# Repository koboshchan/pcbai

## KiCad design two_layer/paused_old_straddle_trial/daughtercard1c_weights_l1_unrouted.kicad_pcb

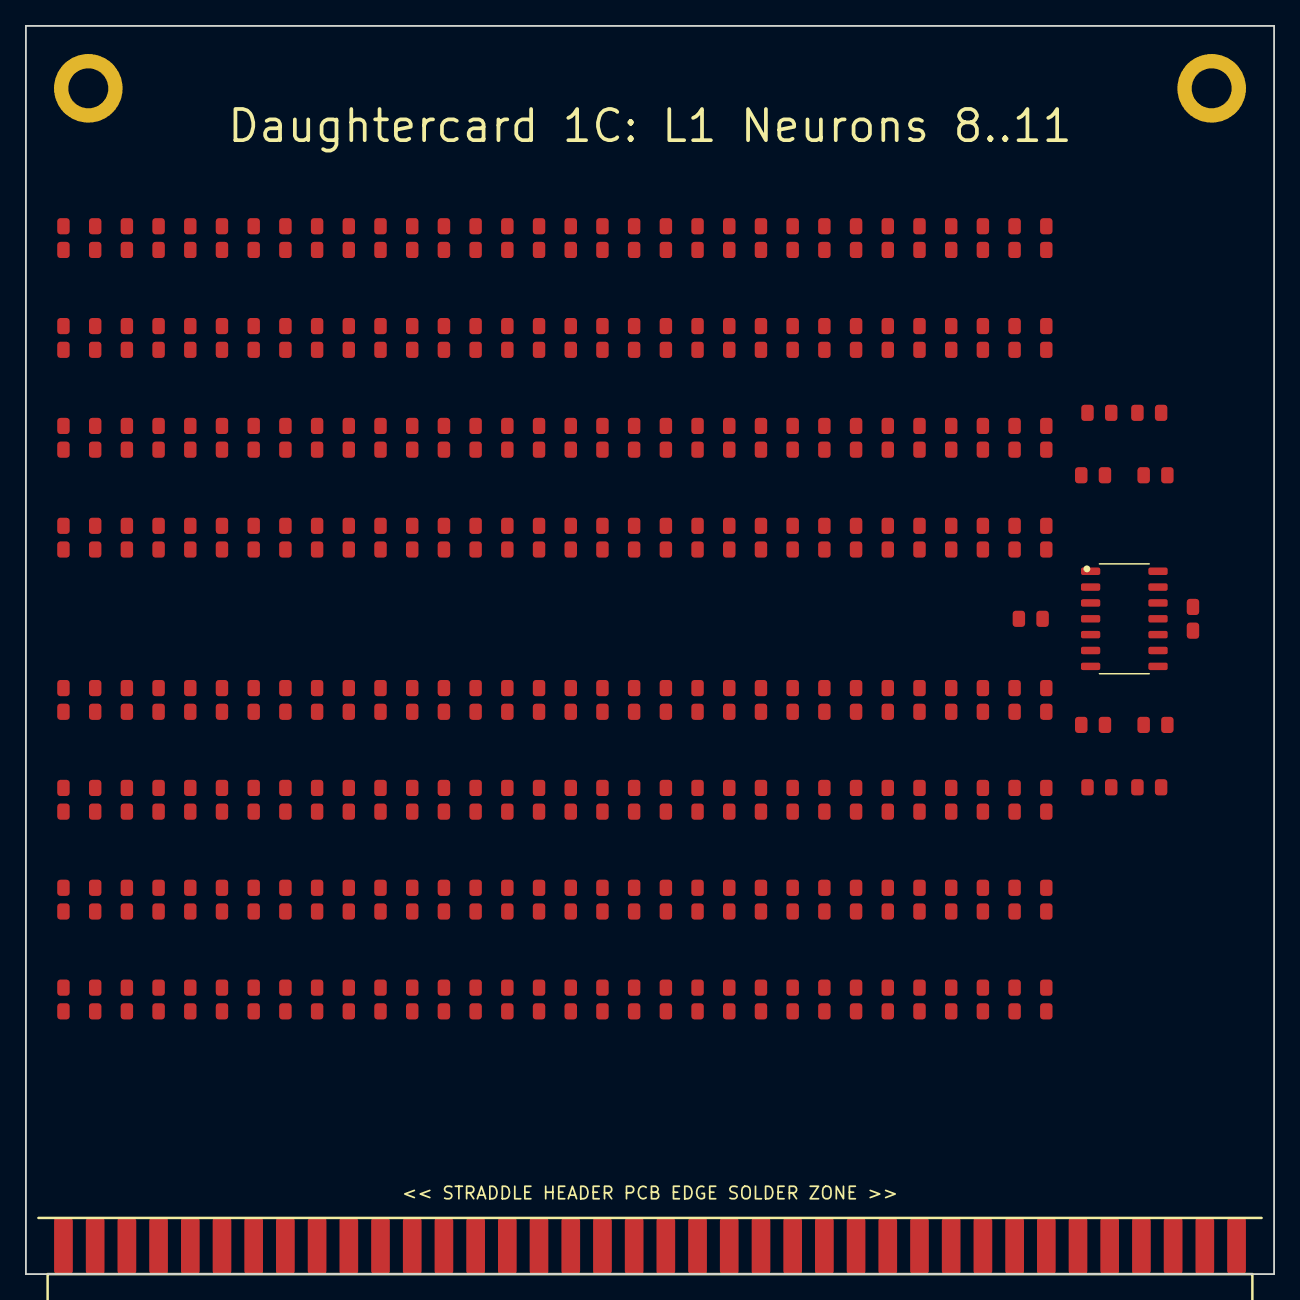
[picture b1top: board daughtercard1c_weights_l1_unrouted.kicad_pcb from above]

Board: 2 copper layers, 100.0 x 100.0 mm, 270 parts (0 on the bottom side), 77 nets, no tracks yet.

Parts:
C_U1N, C_U1P: 0.1uF; C_0805_2012Metric
H1, H2: MountingHole; MountingHole_3.2mm_M3_Pad
J_STRADDLE_EDGE: PinHeader_2x38_Straddle; PinHeader_2x38_Straddle_P2.54mm
R1_0_0, R1_1_0, R1_4_2, R1_5_2, R1_9_1, R1_10_1, R1_11_0, R1_12_0, R1_12_2, R1_16_0, R1_19_1, R1_20_1, R1_22_1, R1_23_2, R1_25_2, R1_28_2, R1_30_0, R1_33_2, R1_37_0, R1_37_2, R1_42_1, R1_44_0, R1_45_1, R1_47_0, R1_47_2, R1_48_0, R1_50_0, R1_51_0, R1_57_2, R1_58_2, R1_59_2, R1_60_1: 33k; R_0805_2012Metric
R1_0_1, R1_3_1, R1_7_0, R1_18_2, R1_32_2, R1_61_1: 5.6k; R_0805_2012Metric
R1_0_2, R1_6_0, R1_6_3, R1_9_0, R1_14_0, R1_20_0, R1_20_3, R1_21_2, R1_27_1, R1_35_2, R1_43_0, R1_52_0, R1_52_1, R1_52_3, R1_54_1, R1_55_2, R1_56_3, R1_58_3, R1_61_0: 75k; R_0805_2012Metric
R1_0_3, R1_1_3, R1_3_3, R1_5_3, R1_15_3, R1_16_3, R1_19_0, R1_26_0, R1_27_0, R1_28_0, R1_29_0, R1_31_2, R1_33_0, R1_34_2, R1_35_1, R1_36_2, R1_37_3, R1_42_0, R1_42_2, R1_43_2, R1_46_3, R1_49_2, R1_49_3, R1_50_1, R1_50_2, R1_52_2, R1_53_0, R1_53_3, R1_54_0, R1_62_0, R1_62_3: 100k; R_0805_2012Metric
R1_1_1, R1_1_2, R1_4_1, R1_8_2, R1_16_2, R1_17_2: 4.7k; R_0805_2012Metric
R1_2_0, R1_5_0, R1_13_2, R1_13_3, R1_22_2, R1_23_1, R1_26_1, R1_29_2, R1_33_3, R1_43_3, R1_51_3, R1_53_2, R1_54_3, R1_59_3, R1_61_2: 47k; R_0805_2012Metric
R1_2_1, R1_4_0, R1_10_0, R1_13_0, R1_17_1, R1_21_1, R1_24_0, R1_28_1, R1_29_1, R1_30_1, R1_33_1, R1_35_0, R1_39_0, R1_43_1, R1_44_1, R1_46_1, R1_58_1, R1_59_1: 22k; R_0805_2012Metric
R1_2_2, R1_5_1, R1_8_1, R1_10_2, R1_32_1, R1_39_1, R1_40_1: 7.5k; R_0805_2012Metric
R1_2_3, R1_3_0, R1_12_3, R1_18_3, R1_21_3, R1_30_2, R1_31_3, R1_34_0, R1_34_3, R1_36_3, R1_38_3, R1_39_3, R1_40_0, R1_40_2, R1_42_3, R1_44_2, R1_47_3, R1_53_1, R1_58_0, R1_61_3: 200k; R_0805_2012Metric
R1_3_2, R1_6_1, R1_11_1, R1_18_0, R1_18_1, R1_24_1, R1_25_1, R1_34_1: 15k; R_0805_2012Metric
R1_4_3, R1_9_3, R1_23_0, R1_25_0, R1_27_3, R1_28_3, R1_36_1, R1_51_1, R1_59_0, R1_60_2, R1_60_3, R1_63_0: 43k; R_0805_2012Metric
R1_6_2, R1_7_3, R1_23_3, R1_24_3, R1_25_3, R1_27_2, R1_31_1, R1_32_3, R1_36_0, R1_38_1, R1_38_2, R1_40_3, R1_41_0, R1_41_2, R1_41_3, R1_44_3, R1_46_2, R1_48_2, R1_48_3, R1_60_0: 51k; R_0805_2012Metric
R1_7_1, R1_47_1, R1_63_2: 3.3k; R_0805_2012Metric
R1_7_2: 3k; R_0805_2012Metric
R1_8_0, R1_15_1, R1_38_0, R1_56_1, R1_57_1: 12k; R_0805_2012Metric
R1_8_3, R1_19_3, R1_26_2, R1_57_3: 470k; R_0805_2012Metric
R1_9_2, R1_11_2, R1_15_0, R1_15_2, R1_16_1, R1_19_2, R1_32_0, R1_56_0, R1_56_2, R1_62_1: 10k; R_0805_2012Metric
R1_10_3, R1_14_2, R1_20_2, R1_41_1, R1_51_2: 1M; R_0805_2012Metric
R1_11_3, R1_30_3, R1_35_3, R1_50_3: 680k; R_0805_2012Metric
R1_12_1, R1_21_0, R1_39_2, R1_45_0, R1_49_1, R1_54_2, R1_57_0, R1_62_2: 20k; R_0805_2012Metric
R1_13_1, R1_14_1, R1_17_0, R1_22_0, R1_46_0, R1_55_0, R1_63_1: 18k; R_0805_2012Metric
R1_14_3, R1_26_3, R1_29_3, R1_31_0, R1_45_2, R1_45_3, R1_48_1: 300k; R_0805_2012Metric
R1_17_3, R1_22_3, R1_63_3: 390k; R_0805_2012Metric
R1_24_2, R1_55_1: 5.1k; R_0805_2012Metric
R1_37_1: DNP; R_0805_2012Metric
R1_49_0, R1_55_3: 10M; R_0805_2012Metric
Rb_N8: 100k; R_0805_2012Metric
Rb_N9: 22k; R_0805_2012Metric
Rb_N10: 680k; R_0805_2012Metric
Rb_N11: DNP; R_0805_2012Metric
Rf_N8, Rf_N9, Rf_N10, Rf_N11: 10k; R_0805_2012Metric
U1: TL074; SOIC-14_3.9x8.7mm_P1.27mm

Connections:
+5V_REF: J_STRADDLE_EDGE.B35, Rb_N11.1
+12V: C_U1P.2, J_STRADDLE_EDGE.B33, J_STRADDLE_EDGE.B34, U1.4
-5V_REF: J_STRADDLE_EDGE.B36, Rb_N8.2, Rb_N9.2, Rb_N10.1
-12V: C_U1N.1, J_STRADDLE_EDGE.B37, J_STRADDLE_EDGE.B38, U1.11
GND: C_U1N.2, C_U1P.1, H1.1, H2.1, J_STRADDLE_EDGE.A37, J_STRADDLE_EDGE.A38, U1.3, U1.5, U1.10, U1.12
INV_N8: R1_0_0.2, R1_1_0.2, R1_2_0.2, R1_3_0.2, R1_4_0.2, R1_5_0.2, R1_6_0.2, R1_7_0.2, R1_8_0.2, R1_9_0.2, R1_10_0.2, R1_11_0.2, R1_12_0.2, R1_13_0.2, R1_14_0.2, R1_15_0.2, R1_16_0.2, R1_17_0.2, R1_18_0.2, R1_19_0.2, R1_20_0.2, R1_21_0.2, R1_22_0.2, R1_23_0.2, R1_24_0.2, R1_25_0.2, R1_26_0.2, R1_27_0.2, R1_28_0.2, R1_29_0.2, R1_30_0.2, R1_31_0.2, R1_32_0.2, R1_33_0.2, R1_34_0.2, R1_35_0.2, R1_36_0.2, R1_37_0.2, R1_38_0.2, R1_39_0.2, R1_40_0.2, R1_41_0.2, R1_42_0.2, R1_43_0.2, R1_44_0.2, R1_45_0.2, R1_46_0.2, R1_47_0.2, R1_48_0.2, R1_49_0.2, R1_50_0.2, R1_51_0.2, R1_52_0.2, R1_53_0.2, R1_54_0.2, R1_55_0.2, R1_56_0.2, R1_57_0.2, R1_58_0.2, R1_59_0.2, R1_60_0.2, R1_61_0.2, R1_62_0.2, R1_63_0.2, Rb_N8.1, Rf_N8.2, U1.2
INV_N9: R1_0_1.2, R1_1_1.2, R1_2_1.2, R1_3_1.2, R1_4_1.2, R1_5_1.2, R1_6_1.2, R1_7_1.2, R1_8_1.2, R1_9_1.2, R1_10_1.2, R1_11_1.2, R1_12_1.2, R1_13_1.2, R1_14_1.2, R1_15_1.2, R1_16_1.2, R1_17_1.2, R1_18_1.2, R1_19_1.2, R1_20_1.2, R1_21_1.2, R1_22_1.2, R1_23_1.2, R1_24_1.2, R1_25_1.2, R1_26_1.2, R1_27_1.2, R1_28_1.2, R1_29_1.2, R1_30_1.2, R1_31_1.2, R1_32_1.2, R1_33_1.2, R1_34_1.2, R1_35_1.2, R1_36_1.2, R1_37_1.2, R1_38_1.2, R1_39_1.2, R1_40_1.2, R1_41_1.2, R1_42_1.2, R1_43_1.2, R1_44_1.2, R1_45_1.2, R1_46_1.2, R1_47_1.2, R1_48_1.2, R1_49_1.2, R1_50_1.2, R1_51_1.2, R1_52_1.2, R1_53_1.2, R1_54_1.2, R1_55_1.2, R1_56_1.2, R1_57_1.2, R1_58_1.2, R1_59_1.2, R1_60_1.2, R1_61_1.2, R1_62_1.2, R1_63_1.2, Rb_N9.1, Rf_N9.2, U1.6
INV_N10: R1_0_2.2, R1_1_2.2, R1_2_2.2, R1_3_2.2, R1_4_2.2, R1_5_2.2, R1_6_2.2, R1_7_2.2, R1_8_2.2, R1_9_2.2, R1_10_2.2, R1_11_2.2, R1_12_2.2, R1_13_2.2, R1_14_2.2, R1_15_2.2, R1_16_2.2, R1_17_2.2, R1_18_2.2, R1_19_2.2, R1_20_2.2, R1_21_2.2, R1_22_2.2, R1_23_2.2, R1_24_2.2, R1_25_2.2, R1_26_2.2, R1_27_2.2, R1_28_2.2, R1_29_2.2, R1_30_2.2, R1_31_2.2, R1_32_2.2, R1_33_2.2, R1_34_2.2, R1_35_2.2, R1_36_2.2, R1_37_2.2, R1_38_2.2, R1_39_2.2, R1_40_2.2, R1_41_2.2, R1_42_2.2, R1_43_2.2, R1_44_2.2, R1_45_2.2, R1_46_2.2, R1_47_2.2, R1_48_2.2, R1_49_2.2, R1_50_2.2, R1_51_2.2, R1_52_2.2, R1_53_2.2, R1_54_2.2, R1_55_2.2, R1_56_2.2, R1_57_2.2, R1_58_2.2, R1_59_2.2, R1_60_2.2, R1_61_2.2, R1_62_2.2, R1_63_2.2, Rb_N10.2, Rf_N10.1, U1.9
INV_N11: R1_0_3.2, R1_1_3.2, R1_2_3.2, R1_3_3.2, R1_4_3.2, R1_5_3.2, R1_6_3.2, R1_7_3.2, R1_8_3.2, R1_9_3.2, R1_10_3.2, R1_11_3.2, R1_12_3.2, R1_13_3.2, R1_14_3.2, R1_15_3.2, R1_16_3.2, R1_17_3.2, R1_18_3.2, R1_19_3.2, R1_20_3.2, R1_21_3.2, R1_22_3.2, R1_23_3.2, R1_24_3.2, R1_25_3.2, R1_26_3.2, R1_27_3.2, R1_28_3.2, R1_29_3.2, R1_30_3.2, R1_31_3.2, R1_32_3.2, R1_33_3.2, R1_34_3.2, R1_35_3.2, R1_36_3.2, R1_37_3.2, R1_38_3.2, R1_39_3.2, R1_40_3.2, R1_41_3.2, R1_42_3.2, R1_43_3.2, R1_44_3.2, R1_45_3.2, R1_46_3.2, R1_47_3.2, R1_48_3.2, R1_49_3.2, R1_50_3.2, R1_51_3.2, R1_52_3.2, R1_53_3.2, R1_54_3.2, R1_55_3.2, R1_56_3.2, R1_57_3.2, R1_58_3.2, R1_59_3.2, R1_60_3.2, R1_61_3.2, R1_62_3.2, R1_63_3.2, Rb_N11.2, Rf_N11.1, U1.13
IN_0: J_STRADDLE_EDGE.A1, R1_0_0.1, R1_0_1.1, R1_0_2.1, R1_0_3.1
IN_1: J_STRADDLE_EDGE.A2, R1_1_0.1, R1_1_1.1, R1_1_2.1, R1_1_3.1
IN_2: J_STRADDLE_EDGE.A3, R1_2_0.1, R1_2_1.1, R1_2_2.1, R1_2_3.1
IN_3: J_STRADDLE_EDGE.A4, R1_3_0.1, R1_3_1.1, R1_3_2.1, R1_3_3.1
IN_4: J_STRADDLE_EDGE.A5, R1_4_0.1, R1_4_1.1, R1_4_2.1, R1_4_3.1
IN_5: J_STRADDLE_EDGE.A6, R1_5_0.1, R1_5_1.1, R1_5_2.1, R1_5_3.1
IN_6: J_STRADDLE_EDGE.A7, R1_6_0.1, R1_6_1.1, R1_6_2.1, R1_6_3.1
IN_7: J_STRADDLE_EDGE.A8, R1_7_0.1, R1_7_1.1, R1_7_2.1, R1_7_3.1
IN_8: J_STRADDLE_EDGE.A9, R1_8_0.1, R1_8_1.1, R1_8_2.1, R1_8_3.1
IN_9: J_STRADDLE_EDGE.A10, R1_9_0.1, R1_9_1.1, R1_9_2.1, R1_9_3.1
IN_10: J_STRADDLE_EDGE.A11, R1_10_0.1, R1_10_1.1, R1_10_2.1, R1_10_3.1
IN_11: J_STRADDLE_EDGE.A12, R1_11_0.1, R1_11_1.1, R1_11_2.1, R1_11_3.1
IN_12: J_STRADDLE_EDGE.A13, R1_12_0.1, R1_12_1.1, R1_12_2.1, R1_12_3.1
IN_13: J_STRADDLE_EDGE.A14, R1_13_0.1, R1_13_1.1, R1_13_2.1, R1_13_3.1
IN_14: J_STRADDLE_EDGE.A15, R1_14_0.1, R1_14_1.1, R1_14_2.1, R1_14_3.1
IN_15: J_STRADDLE_EDGE.A16, R1_15_0.1, R1_15_1.1, R1_15_2.1, R1_15_3.1
IN_16: J_STRADDLE_EDGE.A17, R1_16_0.1, R1_16_1.1, R1_16_2.1, R1_16_3.1
IN_17: J_STRADDLE_EDGE.A18, R1_17_0.1, R1_17_1.1, R1_17_2.1, R1_17_3.1
IN_18: J_STRADDLE_EDGE.A19, R1_18_0.1, R1_18_1.1, R1_18_2.1, R1_18_3.1
IN_19: J_STRADDLE_EDGE.A20, R1_19_0.1, R1_19_1.1, R1_19_2.1, R1_19_3.1
IN_20: J_STRADDLE_EDGE.A21, R1_20_0.1, R1_20_1.1, R1_20_2.1, R1_20_3.1
IN_21: J_STRADDLE_EDGE.A22, R1_21_0.1, R1_21_1.1, R1_21_2.1, R1_21_3.1
IN_22: J_STRADDLE_EDGE.A23, R1_22_0.1, R1_22_1.1, R1_22_2.1, R1_22_3.1
IN_23: J_STRADDLE_EDGE.A24, R1_23_0.1, R1_23_1.1, R1_23_2.1, R1_23_3.1
IN_24: J_STRADDLE_EDGE.A25, R1_24_0.1, R1_24_1.1, R1_24_2.1, R1_24_3.1
IN_25: J_STRADDLE_EDGE.A26, R1_25_0.1, R1_25_1.1, R1_25_2.1, R1_25_3.1
IN_26: J_STRADDLE_EDGE.A27, R1_26_0.1, R1_26_1.1, R1_26_2.1, R1_26_3.1
IN_27: J_STRADDLE_EDGE.A28, R1_27_0.1, R1_27_1.1, R1_27_2.1, R1_27_3.1
IN_28: J_STRADDLE_EDGE.A29, R1_28_0.1, R1_28_1.1, R1_28_2.1, R1_28_3.1
IN_29: J_STRADDLE_EDGE.A30, R1_29_0.1, R1_29_1.1, R1_29_2.1, R1_29_3.1
IN_30: J_STRADDLE_EDGE.A31, R1_30_0.1, R1_30_1.1, R1_30_2.1, R1_30_3.1
IN_31: J_STRADDLE_EDGE.A32, R1_31_0.1, R1_31_1.1, R1_31_2.1, R1_31_3.1
IN_32: J_STRADDLE_EDGE.B1, R1_32_0.1, R1_32_1.1, R1_32_2.1, R1_32_3.1
IN_33: J_STRADDLE_EDGE.B2, R1_33_0.1, R1_33_1.1, R1_33_2.1, R1_33_3.1
IN_34: J_STRADDLE_EDGE.B3, R1_34_0.1, R1_34_1.1, R1_34_2.1, R1_34_3.1
IN_35: J_STRADDLE_EDGE.B4, R1_35_0.1, R1_35_1.1, R1_35_2.1, R1_35_3.1
IN_36: J_STRADDLE_EDGE.B5, R1_36_0.1, R1_36_1.1, R1_36_2.1, R1_36_3.1
IN_37: J_STRADDLE_EDGE.B6, R1_37_0.1, R1_37_1.1, R1_37_2.1, R1_37_3.1
IN_38: J_STRADDLE_EDGE.B7, R1_38_0.1, R1_38_1.1, R1_38_2.1, R1_38_3.1
IN_39: J_STRADDLE_EDGE.B8, R1_39_0.1, R1_39_1.1, R1_39_2.1, R1_39_3.1
IN_40: J_STRADDLE_EDGE.B9, R1_40_0.1, R1_40_1.1, R1_40_2.1, R1_40_3.1
IN_41: J_STRADDLE_EDGE.B10, R1_41_0.1, R1_41_1.1, R1_41_2.1, R1_41_3.1
IN_42: J_STRADDLE_EDGE.B11, R1_42_0.1, R1_42_1.1, R1_42_2.1, R1_42_3.1
IN_43: J_STRADDLE_EDGE.B12, R1_43_0.1, R1_43_1.1, R1_43_2.1, R1_43_3.1
IN_44: J_STRADDLE_EDGE.B13, R1_44_0.1, R1_44_1.1, R1_44_2.1, R1_44_3.1
IN_45: J_STRADDLE_EDGE.B14, R1_45_0.1, R1_45_1.1, R1_45_2.1, R1_45_3.1
IN_46: J_STRADDLE_EDGE.B15, R1_46_0.1, R1_46_1.1, R1_46_2.1, R1_46_3.1
IN_47: J_STRADDLE_EDGE.B16, R1_47_0.1, R1_47_1.1, R1_47_2.1, R1_47_3.1
IN_48: J_STRADDLE_EDGE.B17, R1_48_0.1, R1_48_1.1, R1_48_2.1, R1_48_3.1
IN_49: J_STRADDLE_EDGE.B18, R1_49_0.1, R1_49_1.1, R1_49_2.1, R1_49_3.1
IN_50: J_STRADDLE_EDGE.B19, R1_50_0.1, R1_50_1.1, R1_50_2.1, R1_50_3.1
IN_51: J_STRADDLE_EDGE.B20, R1_51_0.1, R1_51_1.1, R1_51_2.1, R1_51_3.1
IN_52: J_STRADDLE_EDGE.B21, R1_52_0.1, R1_52_1.1, R1_52_2.1, R1_52_3.1
IN_53: J_STRADDLE_EDGE.B22, R1_53_0.1, R1_53_1.1, R1_53_2.1, R1_53_3.1
IN_54: J_STRADDLE_EDGE.B23, R1_54_0.1, R1_54_1.1, R1_54_2.1, R1_54_3.1
IN_55: J_STRADDLE_EDGE.B24, R1_55_0.1, R1_55_1.1, R1_55_2.1, R1_55_3.1
IN_56: J_STRADDLE_EDGE.B25, R1_56_0.1, R1_56_1.1, R1_56_2.1, R1_56_3.1
IN_57: J_STRADDLE_EDGE.B26, R1_57_0.1, R1_57_1.1, R1_57_2.1, R1_57_3.1
IN_58: J_STRADDLE_EDGE.B27, R1_58_0.1, R1_58_1.1, R1_58_2.1, R1_58_3.1
IN_59: J_STRADDLE_EDGE.B28, R1_59_0.1, R1_59_1.1, R1_59_2.1, R1_59_3.1
IN_60: J_STRADDLE_EDGE.B29, R1_60_0.1, R1_60_1.1, R1_60_2.1, R1_60_3.1
IN_61: J_STRADDLE_EDGE.B30, R1_61_0.1, R1_61_1.1, R1_61_2.1, R1_61_3.1
IN_62: J_STRADDLE_EDGE.B31, R1_62_0.1, R1_62_1.1, R1_62_2.1, R1_62_3.1
IN_63: J_STRADDLE_EDGE.B32, R1_63_0.1, R1_63_1.1, R1_63_2.1, R1_63_3.1
V_SUM_8: J_STRADDLE_EDGE.A33, Rf_N8.1, U1.1
V_SUM_9: J_STRADDLE_EDGE.A34, Rf_N9.1, U1.7
V_SUM_10: J_STRADDLE_EDGE.A35, Rf_N10.2, U1.8
V_SUM_11: J_STRADDLE_EDGE.A36, Rf_N11.2, U1.14

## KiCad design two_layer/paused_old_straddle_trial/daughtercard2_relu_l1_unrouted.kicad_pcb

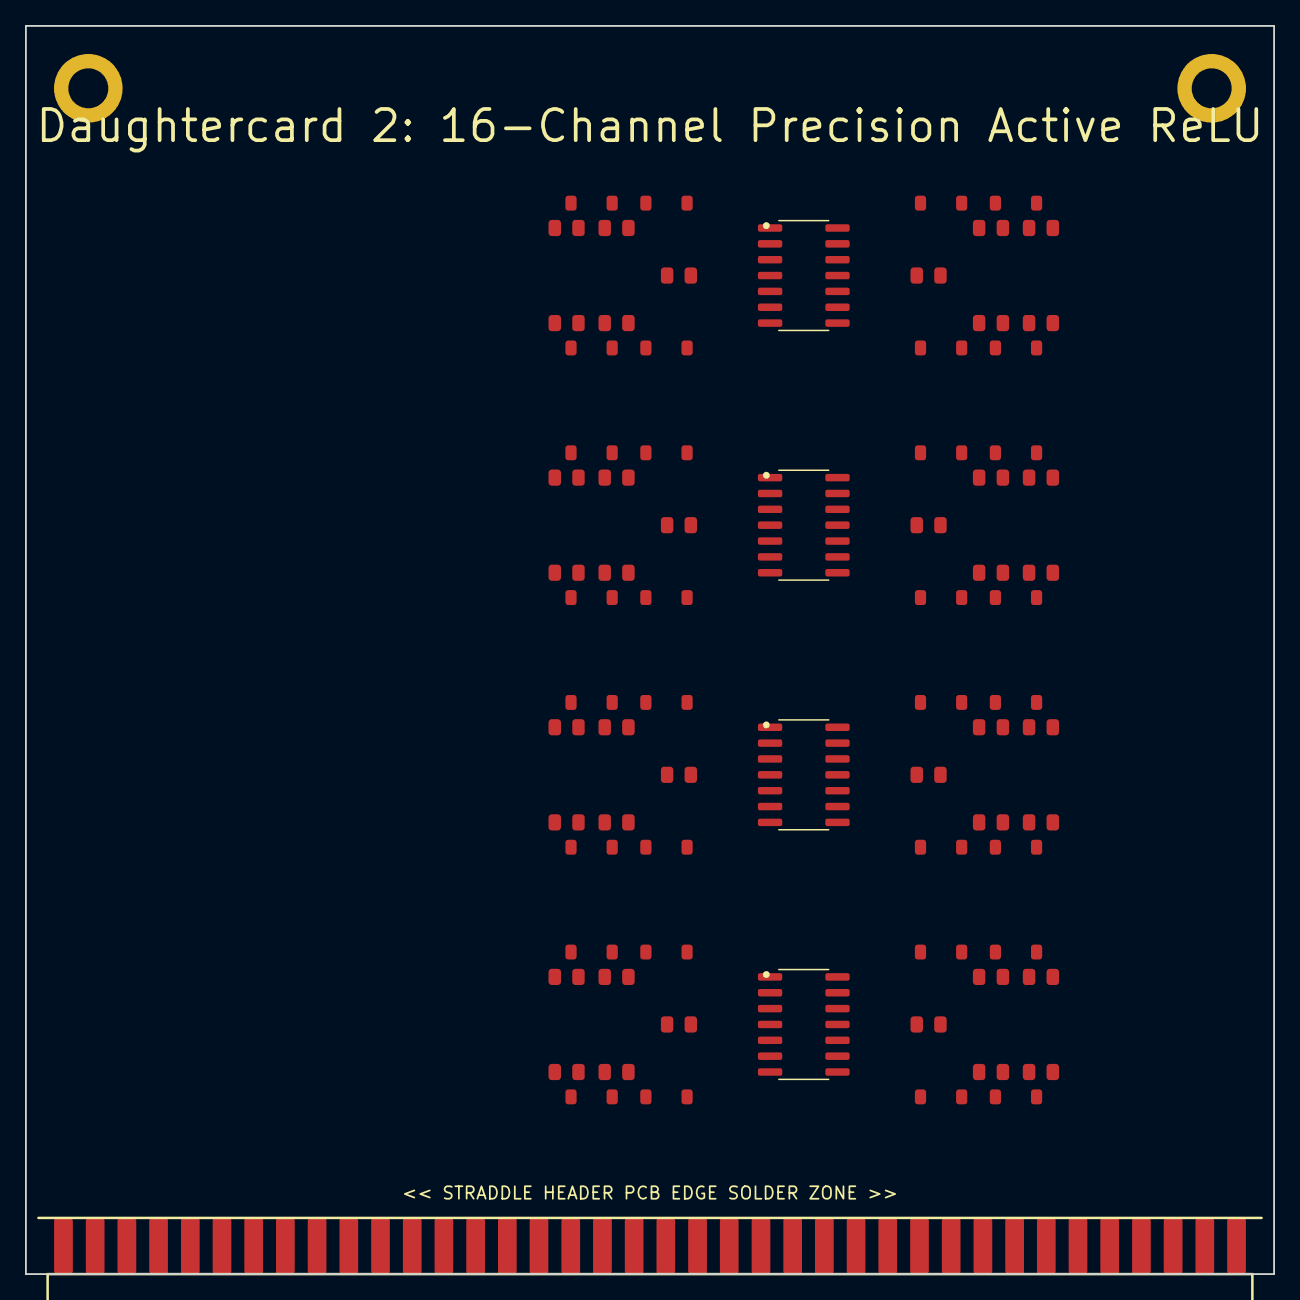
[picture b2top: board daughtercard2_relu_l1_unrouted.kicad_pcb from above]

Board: 2 copper layers, 100.0 x 100.0 mm, 79 parts (0 on the bottom side), 67 nets, no tracks yet.

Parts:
C_U1N, C_U1P, C_U2N, C_U2P, C_U3N, C_U3P, C_U4N, C_U4P: 0.1uF; C_0805_2012Metric
D_CLAMP_0, D_CLAMP_1, D_CLAMP_2, D_CLAMP_3, D_CLAMP_4, D_CLAMP_5, D_CLAMP_6, D_CLAMP_7, D_CLAMP_8, D_CLAMP_9, D_CLAMP_10, D_CLAMP_11, D_CLAMP_12, D_CLAMP_13, D_CLAMP_14, D_CLAMP_15: 1N4148; D_SOD-123
D_RECT_0, D_RECT_1, D_RECT_2, D_RECT_3, D_RECT_4, D_RECT_5, D_RECT_6, D_RECT_7, D_RECT_8, D_RECT_9, D_RECT_10, D_RECT_11, D_RECT_12, D_RECT_13, D_RECT_14, D_RECT_15: 1N4148; D_SOD-123
H1, H2: MountingHole; MountingHole_3.2mm_M3_Pad
J_STRADDLE_EDGE: PinHeader_2x38_Straddle; PinHeader_2x38_Straddle_P2.54mm
R_FB_0, R_FB_1, R_FB_2, R_FB_3, R_FB_4, R_FB_5, R_FB_6, R_FB_7, R_FB_8, R_FB_9, R_FB_10, R_FB_11, R_FB_12, R_FB_13, R_FB_14, R_FB_15: 10k; R_0805_2012Metric
R_IN_0, R_IN_1, R_IN_2, R_IN_3, R_IN_4, R_IN_5, R_IN_6, R_IN_7, R_IN_8, R_IN_9, R_IN_10, R_IN_11, R_IN_12, R_IN_13, R_IN_14, R_IN_15: 10k; R_0805_2012Metric
U1, U2, U3, U4: TL074; SOIC-14_3.9x8.7mm_P1.27mm

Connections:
+12V: C_U1P.2, C_U2P.2, C_U3P.2, C_U4P.2, J_STRADDLE_EDGE.B33, J_STRADDLE_EDGE.B34, U1.4, U2.4, U3.4, U4.4
-12V: C_U1N.1, C_U2N.1, C_U3N.1, C_U4N.1, J_STRADDLE_EDGE.B37, J_STRADDLE_EDGE.B38, U1.11, U2.11, U3.11, U4.11
ACT_0: D_RECT_0.1, J_STRADDLE_EDGE.B1, R_FB_0.2
ACT_1: D_RECT_1.1, J_STRADDLE_EDGE.B2, R_FB_1.1
ACT_2: D_RECT_2.1, J_STRADDLE_EDGE.B3, R_FB_2.2
ACT_3: D_RECT_3.1, J_STRADDLE_EDGE.B4, R_FB_3.1
ACT_4: D_RECT_4.1, J_STRADDLE_EDGE.B5, R_FB_4.2
ACT_5: D_RECT_5.1, J_STRADDLE_EDGE.B6, R_FB_5.1
ACT_6: D_RECT_6.1, J_STRADDLE_EDGE.B7, R_FB_6.2
ACT_7: D_RECT_7.1, J_STRADDLE_EDGE.B8, R_FB_7.1
ACT_8: D_RECT_8.1, J_STRADDLE_EDGE.B9, R_FB_8.2
ACT_9: D_RECT_9.1, J_STRADDLE_EDGE.B10, R_FB_9.1
ACT_10: D_RECT_10.1, J_STRADDLE_EDGE.B11, R_FB_10.2
ACT_11: D_RECT_11.1, J_STRADDLE_EDGE.B12, R_FB_11.1
ACT_12: D_RECT_12.1, J_STRADDLE_EDGE.B13, R_FB_12.2
ACT_13: D_RECT_13.1, J_STRADDLE_EDGE.B14, R_FB_13.1
ACT_14: D_RECT_14.1, J_STRADDLE_EDGE.B15, R_FB_14.2
ACT_15: D_RECT_15.1, J_STRADDLE_EDGE.B16, R_FB_15.1
GND: C_U1N.2, C_U1P.1, C_U2N.2, C_U2P.1, C_U3N.2, C_U3P.1, C_U4N.2, C_U4P.1, H1.1, H2.1, J_STRADDLE_EDGE.A17, J_STRADDLE_EDGE.A18, J_STRADDLE_EDGE.A19, J_STRADDLE_EDGE.A20, J_STRADDLE_EDGE.A21, J_STRADDLE_EDGE.A22, J_STRADDLE_EDGE.A23, J_STRADDLE_EDGE.A24, J_STRADDLE_EDGE.A25, J_STRADDLE_EDGE.A26, J_STRADDLE_EDGE.A27, J_STRADDLE_EDGE.A28, J_STRADDLE_EDGE.A29, J_STRADDLE_EDGE.A30, J_STRADDLE_EDGE.A31, J_STRADDLE_EDGE.A32, J_STRADDLE_EDGE.A33, J_STRADDLE_EDGE.A34, J_STRADDLE_EDGE.A35, J_STRADDLE_EDGE.A36, J_STRADDLE_EDGE.A37, J_STRADDLE_EDGE.A38, J_STRADDLE_EDGE.B17, J_STRADDLE_EDGE.B18, J_STRADDLE_EDGE.B19, J_STRADDLE_EDGE.B20, J_STRADDLE_EDGE.B21, J_STRADDLE_EDGE.B22, J_STRADDLE_EDGE.B23, J_STRADDLE_EDGE.B24, J_STRADDLE_EDGE.B25, J_STRADDLE_EDGE.B26, J_STRADDLE_EDGE.B27, J_STRADDLE_EDGE.B28, J_STRADDLE_EDGE.B29, J_STRADDLE_EDGE.B30, J_STRADDLE_EDGE.B31, J_STRADDLE_EDGE.B32, U1.3, U1.5, U1.10, U1.12, U2.3, U2.5, U2.10, U2.12, U3.3, U3.5, U3.10, U3.12, U4.3, U4.5, U4.10, U4.12
INV_RELU_0: D_CLAMP_0.2, R_FB_0.1, R_IN_0.2, U1.2
INV_RELU_1: D_CLAMP_1.2, R_FB_1.2, R_IN_1.1, U1.13
INV_RELU_2: D_CLAMP_2.2, R_FB_2.1, R_IN_2.2, U1.6
INV_RELU_3: D_CLAMP_3.2, R_FB_3.2, R_IN_3.1, U1.9
INV_RELU_4: D_CLAMP_4.2, R_FB_4.1, R_IN_4.2, U2.2
INV_RELU_5: D_CLAMP_5.2, R_FB_5.2, R_IN_5.1, U2.13
INV_RELU_6: D_CLAMP_6.2, R_FB_6.1, R_IN_6.2, U2.6
INV_RELU_7: D_CLAMP_7.2, R_FB_7.2, R_IN_7.1, U2.9
INV_RELU_8: D_CLAMP_8.2, R_FB_8.1, R_IN_8.2, U3.2
INV_RELU_9: D_CLAMP_9.2, R_FB_9.2, R_IN_9.1, U3.13
INV_RELU_10: D_CLAMP_10.2, R_FB_10.1, R_IN_10.2, U3.6
INV_RELU_11: D_CLAMP_11.2, R_FB_11.2, R_IN_11.1, U3.9
INV_RELU_12: D_CLAMP_12.2, R_FB_12.1, R_IN_12.2, U4.2
INV_RELU_13: D_CLAMP_13.2, R_FB_13.2, R_IN_13.1, U4.13
INV_RELU_14: D_CLAMP_14.2, R_FB_14.1, R_IN_14.2, U4.6
INV_RELU_15: D_CLAMP_15.2, R_FB_15.2, R_IN_15.1, U4.9
OP_OUT_0: D_CLAMP_0.1, D_RECT_0.2, U1.1
OP_OUT_1: D_CLAMP_1.1, D_RECT_1.2, U1.14
OP_OUT_2: D_CLAMP_2.1, D_RECT_2.2, U1.7
OP_OUT_3: D_CLAMP_3.1, D_RECT_3.2, U1.8
OP_OUT_4: D_CLAMP_4.1, D_RECT_4.2, U2.1
OP_OUT_5: D_CLAMP_5.1, D_RECT_5.2, U2.14
OP_OUT_6: D_CLAMP_6.1, D_RECT_6.2, U2.7
OP_OUT_7: D_CLAMP_7.1, D_RECT_7.2, U2.8
OP_OUT_8: D_CLAMP_8.1, D_RECT_8.2, U3.1
OP_OUT_9: D_CLAMP_9.1, D_RECT_9.2, U3.14
OP_OUT_10: D_CLAMP_10.1, D_RECT_10.2, U3.7
OP_OUT_11: D_CLAMP_11.1, D_RECT_11.2, U3.8
OP_OUT_12: D_CLAMP_12.1, D_RECT_12.2, U4.1
OP_OUT_13: D_CLAMP_13.1, D_RECT_13.2, U4.14
OP_OUT_14: D_CLAMP_14.1, D_RECT_14.2, U4.7
OP_OUT_15: D_CLAMP_15.1, D_RECT_15.2, U4.8
V_SUM_0: J_STRADDLE_EDGE.A1, R_IN_0.1
V_SUM_1: J_STRADDLE_EDGE.A2, R_IN_1.2
V_SUM_2: J_STRADDLE_EDGE.A3, R_IN_2.1
V_SUM_3: J_STRADDLE_EDGE.A4, R_IN_3.2
V_SUM_4: J_STRADDLE_EDGE.A5, R_IN_4.1
V_SUM_5: J_STRADDLE_EDGE.A6, R_IN_5.2
V_SUM_6: J_STRADDLE_EDGE.A7, R_IN_6.1
V_SUM_7: J_STRADDLE_EDGE.A8, R_IN_7.2
V_SUM_8: J_STRADDLE_EDGE.A9, R_IN_8.1
V_SUM_9: J_STRADDLE_EDGE.A10, R_IN_9.2
V_SUM_10: J_STRADDLE_EDGE.A11, R_IN_10.1
V_SUM_11: J_STRADDLE_EDGE.A12, R_IN_11.2
V_SUM_12: J_STRADDLE_EDGE.A13, R_IN_12.1
V_SUM_13: J_STRADDLE_EDGE.A14, R_IN_13.2
V_SUM_14: J_STRADDLE_EDGE.A15, R_IN_14.1
V_SUM_15: J_STRADDLE_EDGE.A16, R_IN_15.2

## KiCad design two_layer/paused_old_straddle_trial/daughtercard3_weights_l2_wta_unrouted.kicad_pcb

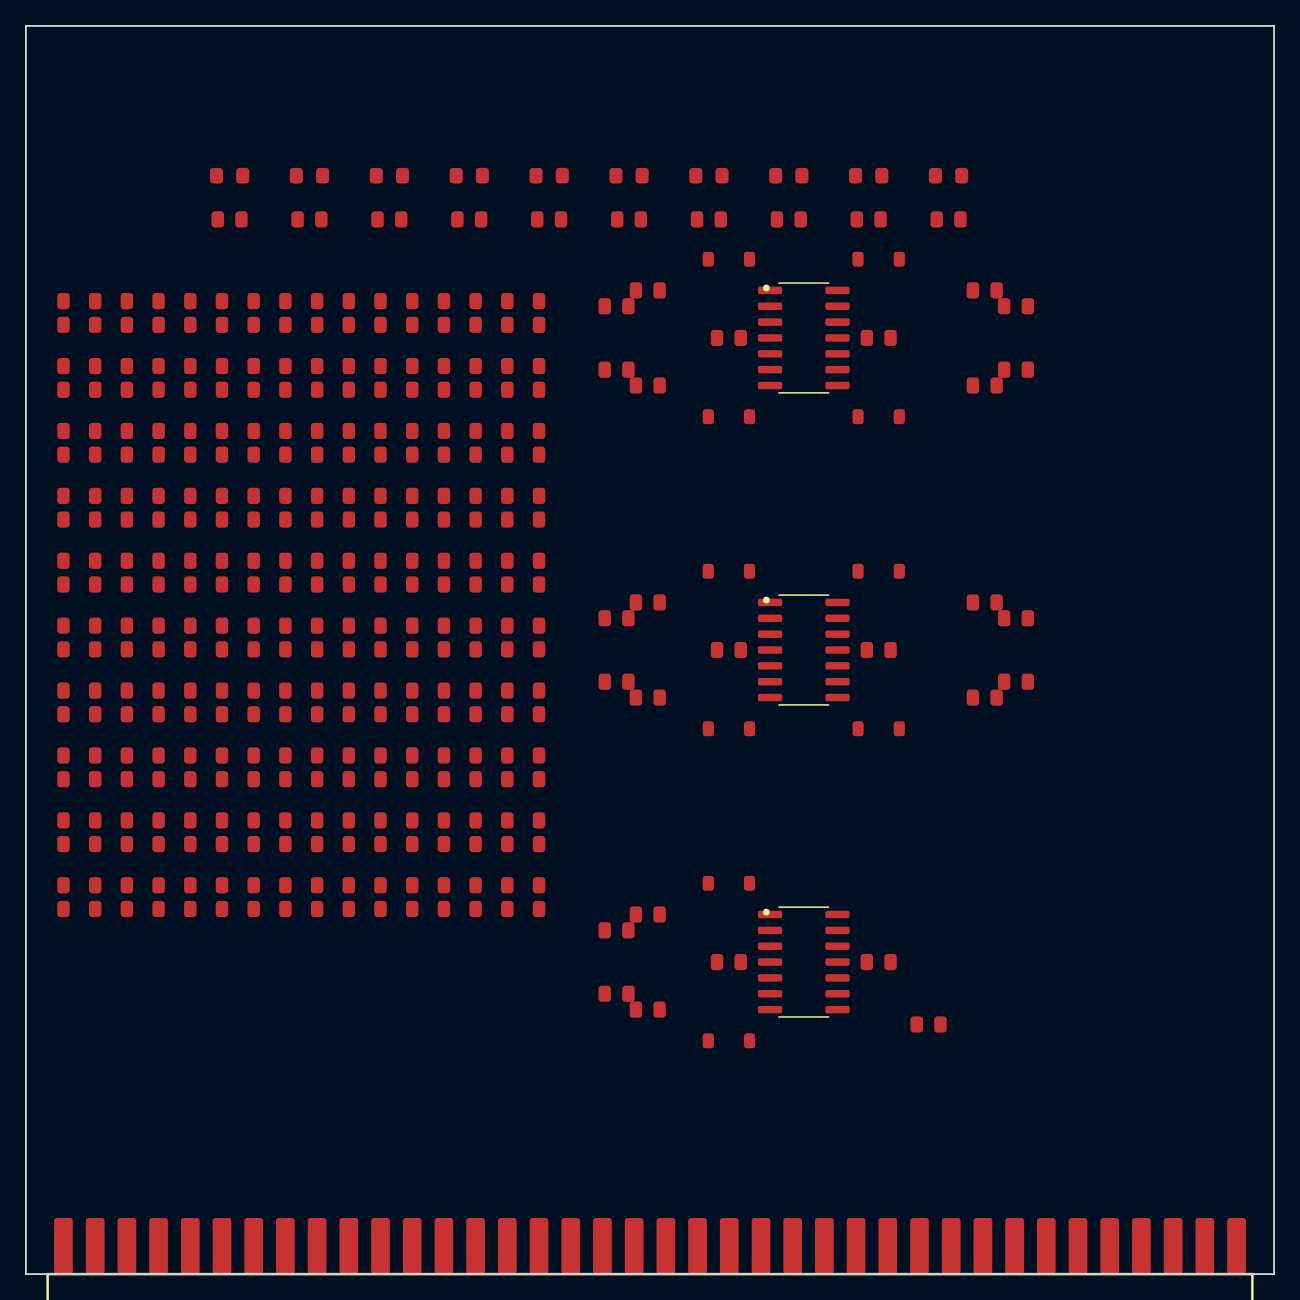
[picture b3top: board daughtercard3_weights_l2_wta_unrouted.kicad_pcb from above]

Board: 2 copper layers, 100.0 x 100.0 mm, 221 parts (0 on the bottom side), 52 nets, no tracks yet.

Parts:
C_U1N, C_U1P, C_U2N, C_U2P, C_U3N, C_U3P: 0.1uF; C_0805_2012Metric
D_LED_0: Digit_0; LED_0805_2012Metric
D_LED_1: Digit_1; LED_0805_2012Metric
D_LED_2: Digit_2; LED_0805_2012Metric
D_LED_3: Digit_3; LED_0805_2012Metric
D_LED_4: Digit_4; LED_0805_2012Metric
D_LED_5: Digit_5; LED_0805_2012Metric
D_LED_6: Digit_6; LED_0805_2012Metric
D_LED_7: Digit_7; LED_0805_2012Metric
D_LED_8: Digit_8; LED_0805_2012Metric
D_LED_9: Digit_9; LED_0805_2012Metric
D_WTA_0, D_WTA_1, D_WTA_2, D_WTA_3, D_WTA_4, D_WTA_5, D_WTA_6, D_WTA_7, D_WTA_8, D_WTA_9: 1N4148; D_SOD-123
J_STRADDLE_EDGE: PinHeader_2x38_Straddle; PinHeader_2x38_Straddle_P2.54mm
R2_0_0, R2_0_1, R2_2_0, R2_3_2, R2_6_5, R2_7_0, R2_8_3, R2_8_8, R2_9_0, R2_10_9: 12k; R_0805_2012Metric
R2_0_2, R2_1_2, R2_1_7, R2_11_1, R2_15_2, R2_15_9: 300k; R_0805_2012Metric
R2_0_3, R2_0_7, R2_0_8, R2_0_9, R2_1_5, R2_2_2, R2_2_5, R2_2_6, R2_2_7, R2_4_7, R2_5_7, R2_7_3, R2_8_0, R2_8_7, R2_8_9, R2_9_6, R2_9_8, R2_12_5, R2_13_4, R2_14_6, R2_14_9: 33k; R_0805_2012Metric
R2_0_4, R2_2_3, R2_3_1, R2_3_4, R2_4_4, R2_4_5, R2_5_3, R2_5_5, R2_6_2, R2_6_9, R2_7_7, R2_8_2, R2_9_2, R2_10_3, R2_12_1, R2_12_4, R2_12_9, R2_14_7: 22k; R_0805_2012Metric
R2_0_5, R2_0_6, R2_2_1, R2_5_1, R2_5_6, R2_7_2, R2_7_5, R2_7_9: 7.5k; R_0805_2012Metric
R2_1_0, R2_1_6, R2_1_8, R2_2_8, R2_3_5, R2_4_2, R2_9_5, R2_11_2, R2_11_7, R2_11_9, R2_13_5, R2_13_6, R2_13_7, R2_15_3, R2_15_7, R2_15_8: 75k; R_0805_2012Metric
R2_1_1, R2_1_3, R2_1_9, R2_2_4, R2_10_5, R2_11_4, R2_14_0, R2_15_4: 51k; R_0805_2012Metric
R2_1_4, R2_2_9, R2_5_8, R2_8_4, R2_11_0, R2_11_5, R2_11_6, R2_11_8, R2_12_0, R2_12_8, R2_13_1, R2_13_8, R2_14_5, R2_15_0, R2_15_6: 100k; R_0805_2012Metric
R2_3_0, R2_4_1, R2_10_6, R2_14_1, R2_14_4, R2_14_8: 15k; R_0805_2012Metric
R2_3_3, R2_3_7, R2_3_8, R2_4_6, R2_6_6, R2_6_7, R2_7_1, R2_9_3, R2_10_8, R2_12_3, R2_13_2, R2_14_2: 43k; R_0805_2012Metric
R2_3_6, R2_4_8, R2_6_4, R2_7_4, R2_9_1, R2_10_1: 10k; R_0805_2012Metric
R2_3_9, R2_5_2, R2_5_4, R2_5_9, R2_7_6, R2_8_6, R2_10_7, R2_12_6: 20k; R_0805_2012Metric
R2_4_0, R2_4_3, R2_14_3: 390k; R_0805_2012Metric
R2_4_9, R2_7_8, R2_11_3, R2_12_2, R2_13_3, R2_13_9, R2_15_1: 200k; R_0805_2012Metric
R2_5_0, R2_6_1: 5.6k; R_0805_2012Metric
R2_6_0, R2_8_1, R2_9_4, R2_9_9, R2_10_2: 18k; R_0805_2012Metric
R2_6_3, R2_9_7: 47k; R_0805_2012Metric
R2_6_8, R2_13_0: 680k; R_0805_2012Metric
R2_8_5, R2_15_5: 1M; R_0805_2012Metric
R2_10_0: 10M; R_0805_2012Metric
R2_10_4: 3.3k; R_0805_2012Metric
R2_12_7: 5.1k; R_0805_2012Metric
R_LED_0, R_LED_1, R_LED_2, R_LED_3, R_LED_4, R_LED_5, R_LED_6, R_LED_7, R_LED_8, R_LED_9: 1k; R_0805_2012Metric
R_WTA: 10k; R_0805_2012Metric
Rb_L2_0, Rb_L2_6: 33k; R_0805_2012Metric
Rb_L2_1, Rb_L2_3: 18k; R_0805_2012Metric
Rb_L2_2, Rb_L2_4: 75k; R_0805_2012Metric
Rb_L2_5, Rb_L2_7: 100k; R_0805_2012Metric
Rb_L2_8: 470k; R_0805_2012Metric
Rb_L2_9: 43k; R_0805_2012Metric
Rf_L2_0, Rf_L2_1, Rf_L2_2, Rf_L2_3, Rf_L2_4, Rf_L2_5, Rf_L2_6, Rf_L2_7, Rf_L2_8, Rf_L2_9: 10k; R_0805_2012Metric
U1, U2, U3: TL074; SOIC-14_3.9x8.7mm_P1.27mm

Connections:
+5V_REF: J_STRADDLE_EDGE.B35, Rb_L2_3.1, Rb_L2_4.1, Rb_L2_5.1, Rb_L2_9.2
+12V: C_U1P.2, C_U2P.2, C_U3P.2, J_STRADDLE_EDGE.B33, J_STRADDLE_EDGE.B34, U1.4, U2.4, U3.4
-5V_REF: J_STRADDLE_EDGE.B36, Rb_L2_0.1, Rb_L2_1.1, Rb_L2_2.1, Rb_L2_6.2, Rb_L2_7.2, Rb_L2_8.2
-12V: C_U1N.1, C_U2N.1, C_U3N.1, J_STRADDLE_EDGE.B37, J_STRADDLE_EDGE.B38, R_WTA.2, U1.11, U2.11, U3.11
ACT_0: J_STRADDLE_EDGE.A1, R2_0_0.1, R2_0_1.1, R2_0_2.1, R2_0_3.1, R2_0_4.1, R2_0_5.1, R2_0_6.1, R2_0_7.1, R2_0_8.1, R2_0_9.1
ACT_1: J_STRADDLE_EDGE.A2, R2_1_0.1, R2_1_1.1, R2_1_2.1, R2_1_3.1, R2_1_4.1, R2_1_5.1, R2_1_6.1, R2_1_7.1, R2_1_8.1, R2_1_9.1
ACT_2: J_STRADDLE_EDGE.A3, R2_2_0.1, R2_2_1.1, R2_2_2.1, R2_2_3.1, R2_2_4.1, R2_2_5.1, R2_2_6.1, R2_2_7.1, R2_2_8.1, R2_2_9.1
ACT_3: J_STRADDLE_EDGE.A4, R2_3_0.1, R2_3_1.1, R2_3_2.1, R2_3_3.1, R2_3_4.1, R2_3_5.1, R2_3_6.1, R2_3_7.1, R2_3_8.1, R2_3_9.1
ACT_4: J_STRADDLE_EDGE.A5, R2_4_0.1, R2_4_1.1, R2_4_2.1, R2_4_3.1, R2_4_4.1, R2_4_5.1, R2_4_6.1, R2_4_7.1, R2_4_8.1, R2_4_9.1
ACT_5: J_STRADDLE_EDGE.A6, R2_5_0.1, R2_5_1.1, R2_5_2.1, R2_5_3.1, R2_5_4.1, R2_5_5.1, R2_5_6.1, R2_5_7.1, R2_5_8.1, R2_5_9.1
ACT_6: J_STRADDLE_EDGE.A7, R2_6_0.1, R2_6_1.1, R2_6_2.1, R2_6_3.1, R2_6_4.1, R2_6_5.1, R2_6_6.1, R2_6_7.1, R2_6_8.1, R2_6_9.1
ACT_7: J_STRADDLE_EDGE.A8, R2_7_0.1, R2_7_1.1, R2_7_2.1, R2_7_3.1, R2_7_4.1, R2_7_5.1, R2_7_6.1, R2_7_7.1, R2_7_8.1, R2_7_9.1
ACT_8: J_STRADDLE_EDGE.A9, R2_8_0.1, R2_8_1.1, R2_8_2.1, R2_8_3.1, R2_8_4.1, R2_8_5.1, R2_8_6.1, R2_8_7.1, R2_8_8.1, R2_8_9.1
ACT_9: J_STRADDLE_EDGE.A10, R2_9_0.1, R2_9_1.1, R2_9_2.1, R2_9_3.1, R2_9_4.1, R2_9_5.1, R2_9_6.1, R2_9_7.1, R2_9_8.1, R2_9_9.1
ACT_10: J_STRADDLE_EDGE.A11, R2_10_0.1, R2_10_1.1, R2_10_2.1, R2_10_3.1, R2_10_4.1, R2_10_5.1, R2_10_6.1, R2_10_7.1, R2_10_8.1, R2_10_9.1
ACT_11: J_STRADDLE_EDGE.A12, R2_11_0.1, R2_11_1.1, R2_11_2.1, R2_11_3.1, R2_11_4.1, R2_11_5.1, R2_11_6.1, R2_11_7.1, R2_11_8.1, R2_11_9.1
ACT_12: J_STRADDLE_EDGE.A13, R2_12_0.1, R2_12_1.1, R2_12_2.1, R2_12_3.1, R2_12_4.1, R2_12_5.1, R2_12_6.1, R2_12_7.1, R2_12_8.1, R2_12_9.1
ACT_13: J_STRADDLE_EDGE.A14, R2_13_0.1, R2_13_1.1, R2_13_2.1, R2_13_3.1, R2_13_4.1, R2_13_5.1, R2_13_6.1, R2_13_7.1, R2_13_8.1, R2_13_9.1
ACT_14: J_STRADDLE_EDGE.A15, R2_14_0.1, R2_14_1.1, R2_14_2.1, R2_14_3.1, R2_14_4.1, R2_14_5.1, R2_14_6.1, R2_14_7.1, R2_14_8.1, R2_14_9.1
ACT_15: J_STRADDLE_EDGE.A16, R2_15_0.1, R2_15_1.1, R2_15_2.1, R2_15_3.1, R2_15_4.1, R2_15_5.1, R2_15_6.1, R2_15_7.1, R2_15_8.1, R2_15_9.1
GND: C_U1N.2, C_U1P.1, C_U2N.2, C_U2P.1, C_U3N.2, C_U3P.1, J_STRADDLE_EDGE.A17, J_STRADDLE_EDGE.A18, J_STRADDLE_EDGE.A19, J_STRADDLE_EDGE.A20, J_STRADDLE_EDGE.A21, J_STRADDLE_EDGE.A22, J_STRADDLE_EDGE.A23, J_STRADDLE_EDGE.A24, J_STRADDLE_EDGE.A25, J_STRADDLE_EDGE.A26, J_STRADDLE_EDGE.A27, J_STRADDLE_EDGE.A28, J_STRADDLE_EDGE.A29, J_STRADDLE_EDGE.A30, J_STRADDLE_EDGE.A31, J_STRADDLE_EDGE.A32, J_STRADDLE_EDGE.A33, J_STRADDLE_EDGE.A34, J_STRADDLE_EDGE.A35, J_STRADDLE_EDGE.A36, J_STRADDLE_EDGE.A37, J_STRADDLE_EDGE.A38, J_STRADDLE_EDGE.B11, J_STRADDLE_EDGE.B12, J_STRADDLE_EDGE.B13, J_STRADDLE_EDGE.B14, J_STRADDLE_EDGE.B15, J_STRADDLE_EDGE.B16, J_STRADDLE_EDGE.B17, J_STRADDLE_EDGE.B18, J_STRADDLE_EDGE.B19, J_STRADDLE_EDGE.B20, J_STRADDLE_EDGE.B21, J_STRADDLE_EDGE.B22, J_STRADDLE_EDGE.B23, J_STRADDLE_EDGE.B24, J_STRADDLE_EDGE.B25, J_STRADDLE_EDGE.B26, J_STRADDLE_EDGE.B27, J_STRADDLE_EDGE.B28, J_STRADDLE_EDGE.B29, J_STRADDLE_EDGE.B30, J_STRADDLE_EDGE.B31, J_STRADDLE_EDGE.B32, R_LED_0.2, R_LED_1.2, R_LED_2.2, R_LED_3.2, R_LED_4.2, R_LED_5.2, R_LED_6.2, R_LED_7.2, R_LED_8.2, R_LED_9.2, U1.3, U1.5, U1.10, U1.12, U2.3, U2.5, U2.10, U2.12, U3.3, U3.5, U3.8, U3.9, U3.10, U3.12, U3.13, U3.14
INV_L2_0: R2_0_0.2, R2_1_0.2, R2_2_0.2, R2_3_0.2, R2_4_0.2, R2_5_0.2, R2_6_0.2, R2_7_0.2, R2_8_0.2, R2_9_0.2, R2_10_0.2, R2_11_0.2, R2_12_0.2, R2_13_0.2, R2_14_0.2, R2_15_0.2, Rb_L2_0.2, Rf_L2_0.1, U1.2
INV_L2_1: R2_0_1.2, R2_1_1.2, R2_2_1.2, R2_3_1.2, R2_4_1.2, R2_5_1.2, R2_6_1.2, R2_7_1.2, R2_8_1.2, R2_9_1.2, R2_10_1.2, R2_11_1.2, R2_12_1.2, R2_13_1.2, R2_14_1.2, R2_15_1.2, Rb_L2_1.2, Rf_L2_1.1, U1.6
INV_L2_2: R2_0_2.2, R2_1_2.2, R2_2_2.2, R2_3_2.2, R2_4_2.2, R2_5_2.2, R2_6_2.2, R2_7_2.2, R2_8_2.2, R2_9_2.2, R2_10_2.2, R2_11_2.2, R2_12_2.2, R2_13_2.2, R2_14_2.2, R2_15_2.2, Rb_L2_2.2, Rf_L2_2.1, U2.2
INV_L2_3: R2_0_3.2, R2_1_3.2, R2_2_3.2, R2_3_3.2, R2_4_3.2, R2_5_3.2, R2_6_3.2, R2_7_3.2, R2_8_3.2, R2_9_3.2, R2_10_3.2, R2_11_3.2, R2_12_3.2, R2_13_3.2, R2_14_3.2, R2_15_3.2, Rb_L2_3.2, Rf_L2_3.1, U2.6
INV_L2_4: R2_0_4.2, R2_1_4.2, R2_2_4.2, R2_3_4.2, R2_4_4.2, R2_5_4.2, R2_6_4.2, R2_7_4.2, R2_8_4.2, R2_9_4.2, R2_10_4.2, R2_11_4.2, R2_12_4.2, R2_13_4.2, R2_14_4.2, R2_15_4.2, Rb_L2_4.2, Rf_L2_4.1, U3.2
INV_L2_5: R2_0_5.2, R2_1_5.2, R2_2_5.2, R2_3_5.2, R2_4_5.2, R2_5_5.2, R2_6_5.2, R2_7_5.2, R2_8_5.2, R2_9_5.2, R2_10_5.2, R2_11_5.2, R2_12_5.2, R2_13_5.2, R2_14_5.2, R2_15_5.2, Rb_L2_5.2, Rf_L2_5.1, U3.6
INV_L2_6: R2_0_6.2, R2_1_6.2, R2_2_6.2, R2_3_6.2, R2_4_6.2, R2_5_6.2, R2_6_6.2, R2_7_6.2, R2_8_6.2, R2_9_6.2, R2_10_6.2, R2_11_6.2, R2_12_6.2, R2_13_6.2, R2_14_6.2, R2_15_6.2, Rb_L2_6.1, Rf_L2_6.2, U1.13
INV_L2_7: R2_0_7.2, R2_1_7.2, R2_2_7.2, R2_3_7.2, R2_4_7.2, R2_5_7.2, R2_6_7.2, R2_7_7.2, R2_8_7.2, R2_9_7.2, R2_10_7.2, R2_11_7.2, R2_12_7.2, R2_13_7.2, R2_14_7.2, R2_15_7.2, Rb_L2_7.1, Rf_L2_7.2, U1.9
INV_L2_8: R2_0_8.2, R2_1_8.2, R2_2_8.2, R2_3_8.2, R2_4_8.2, R2_5_8.2, R2_6_8.2, R2_7_8.2, R2_8_8.2, R2_9_8.2, R2_10_8.2, R2_11_8.2, R2_12_8.2, R2_13_8.2, R2_14_8.2, R2_15_8.2, Rb_L2_8.1, Rf_L2_8.2, U2.13
INV_L2_9: R2_0_9.2, R2_1_9.2, R2_2_9.2, R2_3_9.2, R2_4_9.2, R2_5_9.2, R2_6_9.2, R2_7_9.2, R2_8_9.2, R2_9_9.2, R2_10_9.2, R2_11_9.2, R2_12_9.2, R2_13_9.2, R2_14_9.2, R2_15_9.2, Rb_L2_9.1, Rf_L2_9.2, U2.9
LED_N_0: D_LED_0.2, R_LED_0.1
LED_N_1: D_LED_1.2, R_LED_1.1
LED_N_2: D_LED_2.2, R_LED_2.1
LED_N_3: D_LED_3.2, R_LED_3.1
LED_N_4: D_LED_4.2, R_LED_4.1
LED_N_5: D_LED_5.2, R_LED_5.1
LED_N_6: D_LED_6.2, R_LED_6.1
LED_N_7: D_LED_7.2, R_LED_7.1
LED_N_8: D_LED_8.2, R_LED_8.1
LED_N_9: D_LED_9.2, R_LED_9.1
SCORE_0: D_LED_0.1, D_WTA_0.2, J_STRADDLE_EDGE.B1, Rf_L2_0.2, U1.1
SCORE_1: D_LED_1.1, D_WTA_1.2, J_STRADDLE_EDGE.B2, Rf_L2_1.2, U1.7
SCORE_2: D_LED_2.1, D_WTA_2.2, J_STRADDLE_EDGE.B3, Rf_L2_2.2, U2.1
SCORE_3: D_LED_3.1, D_WTA_3.2, J_STRADDLE_EDGE.B4, Rf_L2_3.2, U2.7
SCORE_4: D_LED_4.1, D_WTA_4.2, J_STRADDLE_EDGE.B5, Rf_L2_4.2, U3.1
SCORE_5: D_LED_5.1, D_WTA_5.2, J_STRADDLE_EDGE.B6, Rf_L2_5.2, U3.7
SCORE_6: D_LED_6.1, D_WTA_6.2, J_STRADDLE_EDGE.B7, Rf_L2_6.1, U1.14
SCORE_7: D_LED_7.1, D_WTA_7.2, J_STRADDLE_EDGE.B8, Rf_L2_7.1, U1.8
SCORE_8: D_LED_8.1, D_WTA_8.2, J_STRADDLE_EDGE.B9, Rf_L2_8.1, U2.14
SCORE_9: D_LED_9.1, D_WTA_9.2, J_STRADDLE_EDGE.B10, Rf_L2_9.1, U2.8
WTA_BUS: D_WTA_0.1, D_WTA_1.1, D_WTA_2.1, D_WTA_3.1, D_WTA_4.1, D_WTA_5.1, D_WTA_6.1, D_WTA_7.1, D_WTA_8.1, D_WTA_9.1, R_WTA.1
